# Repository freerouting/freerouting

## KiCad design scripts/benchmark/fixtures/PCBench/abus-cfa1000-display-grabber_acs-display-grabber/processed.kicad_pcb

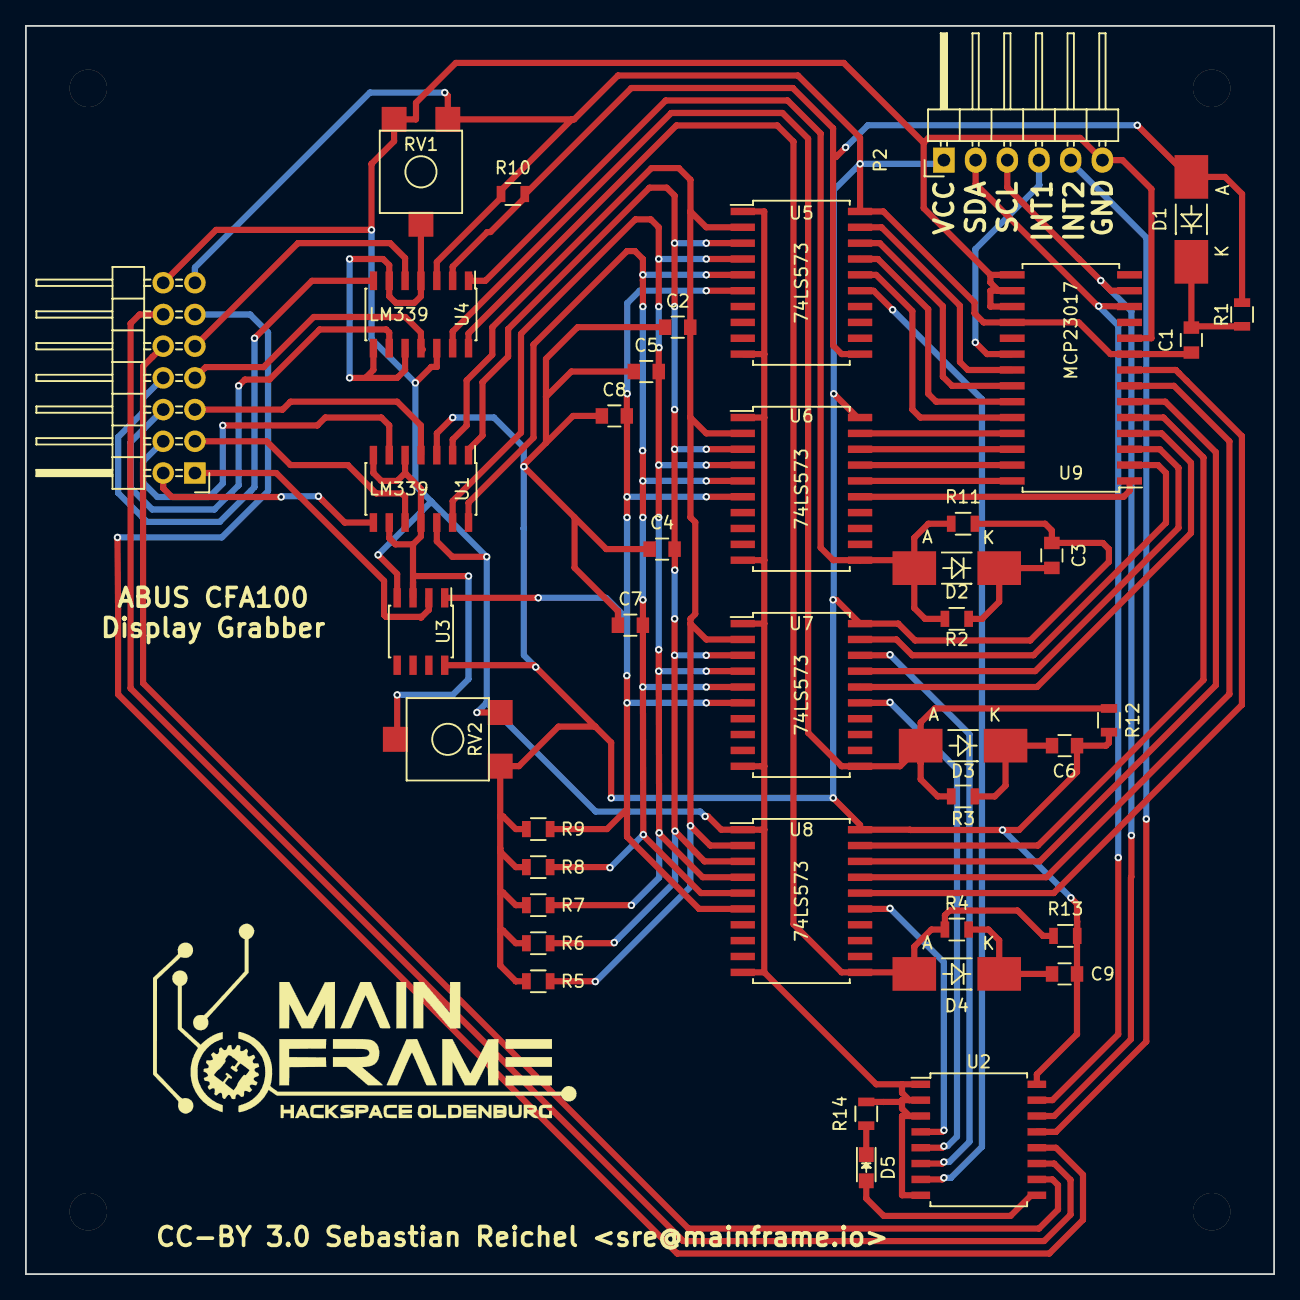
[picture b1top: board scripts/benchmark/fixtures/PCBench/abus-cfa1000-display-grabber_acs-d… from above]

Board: 2 copper layers, 100.0 x 100.0 mm, 41 parts (0 on the bottom side), 55 nets.

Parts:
C1, C3, C6, C9: 20nF; C_0805
C2, C4, C5, C7, C8: 10nF; C_0805
D1, D2, D3, D4: 1N4007; MELF_Handsoldering
D5: Red LED; LED_0805
P1: CONN_02X07; Pin_Header_Angled_2x07
P2: CONN_01X06; Pin_Header_Angled_1x06
R1, R2, R3, R4: 1.8K; R_0805
R5, R6, R7, R8, R9, R10, R11, R12, R13: 3.3K; R_0805
R14: 150; R_0805
RV1, RV2: POT; ACP_CA6
U1, U4: LM339; SOIC-14_3.9x8.7mm_Pitch1.27mm
U2: PCF8574; SOIC-16_7.5x10.3mm_Pitch1.27mm
U3: LM393; SOIC-8_3.9x4.9mm_Pitch1.27mm
U5, U6, U7, U8: 74LS573; SOIC-20_7.5x12.8mm_Pitch1.27mm
U9: MCP23017; SOIC-28_7.5x17.9mm_Pitch1.27mm

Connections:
+5V: C1.2, C2.1, C3.2, C4.1, C5.1, C6.2, C7.1, C8.1, C9.2, P1.13, P2.1, R5.1, R6.1, R7.1, R8.1, R9.1, R10.1, R11.1, R12.1, R13.1, RV1.1, RV2.1, U1.3, U2.16, U3.8, U4.3, U5.20, U6.20, U7.20, U8.20, U9.9, U9.18
/COM0: P1.9, U4.5
/COM0_SEG4: U2.7, U5.15
/COM0clean: D1.2, R1.1, R10.2, U4.2, U5.11
/COM1: P1.8, U4.7
/COM1clean: D2.2, R2.1, R11.2, U4.1, U6.11
/COM2: P1.7, U4.11
/COM2clean: D3.2, R3.1, R12.2, U4.13, U7.11
/COM3: P1.6, U4.9
/COM3_SEG1: U2.6, U7.18
/COM3_SEG4: U2.5, U7.15
/COM3clean: D4.2, R4.1, R13.2, U4.14, U8.11
/COM4_SEG4: U2.4, U8.15
/INT1: P2.4, U9.20
/INT2: P2.5, U2.13
/LED: D5.2, U2.9
/LOCK: P1.10, U2.10
/SCL: P2.3, U2.14, U9.13
/SDA: P2.2, U2.15, U9.12
/SEG0: P1.5, U1.4
/SEG0clean: C2.2, R5.2, U1.2, U5.2, U6.2, U7.2, U8.2
/SEG1: P1.4, U1.6
/SEG1clean: C4.2, R6.2, U1.1, U5.3, U6.3, U7.3, U8.3
/SEG2: P1.3, U1.10
/SEG2clean: C5.2, R7.2, U1.13, U5.4, U6.4, U7.4, U8.4
/SEG3: P1.2, U1.8
/SEG3clean: C7.2, R8.2, U1.14, U5.5, U6.5, U7.5, U8.5
/SEG4: P1.1, U3.2
/SEG4clean: C8.2, R9.2, U3.1, U5.6, U6.6, U7.6, U8.6
/SETUP: P1.11, U2.12
/UNLOCK: P1.12, U2.11
/Vhigh: RV1.2, U4.4, U4.6, U4.8, U4.10
/Vlow: RV2.2, U1.5, U1.7, U1.9, U1.11, U3.3
GND: P1.14, P2.6, R14.2, RV1.3, RV2.3, U1.12, U2.1, U2.2, U2.3, U2.8, U3.4, U4.12, U5.1, U5.10, U6.1, U6.10, U7.1, U7.10, U8.1, U8.10, U9.10, U9.15, U9.16, U9.17
unnamed: C1.1, D1.1, R1.2
unnamed: C3.1, D2.1, R2.2
unnamed: C6.1, D3.1, R3.2
unnamed: C9.1, D4.1, R4.2
unnamed: D5.1, R14.1
unnamed: U5.16, U9.24
unnamed: U5.17, U9.23
unnamed: U5.18, U9.22
unnamed: U5.19, U9.21
unnamed: U6.15, U9.1
unnamed: U6.16, U9.28
unnamed: U6.17, U9.27
unnamed: U6.18, U9.26
unnamed: U6.19, U9.25
unnamed: U7.16, U9.4
unnamed: U7.17, U9.3
unnamed: U7.19, U9.2
unnamed: U8.16, U9.8
unnamed: U8.17, U9.7
unnamed: U8.18, U9.6
unnamed: U8.19, U9.5

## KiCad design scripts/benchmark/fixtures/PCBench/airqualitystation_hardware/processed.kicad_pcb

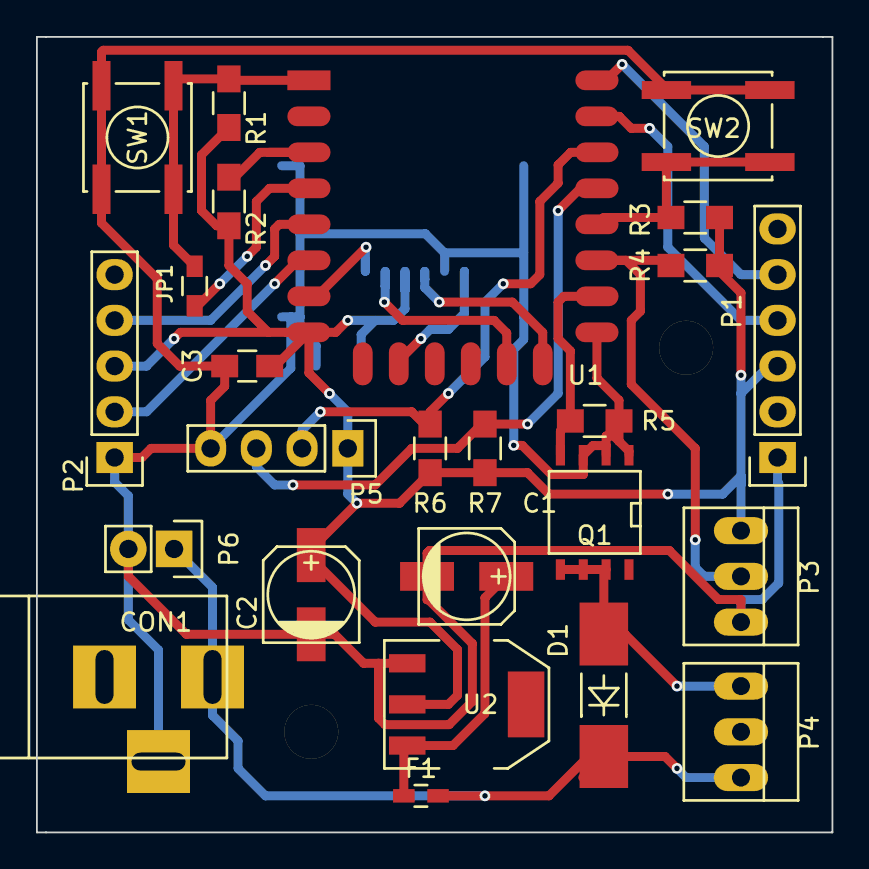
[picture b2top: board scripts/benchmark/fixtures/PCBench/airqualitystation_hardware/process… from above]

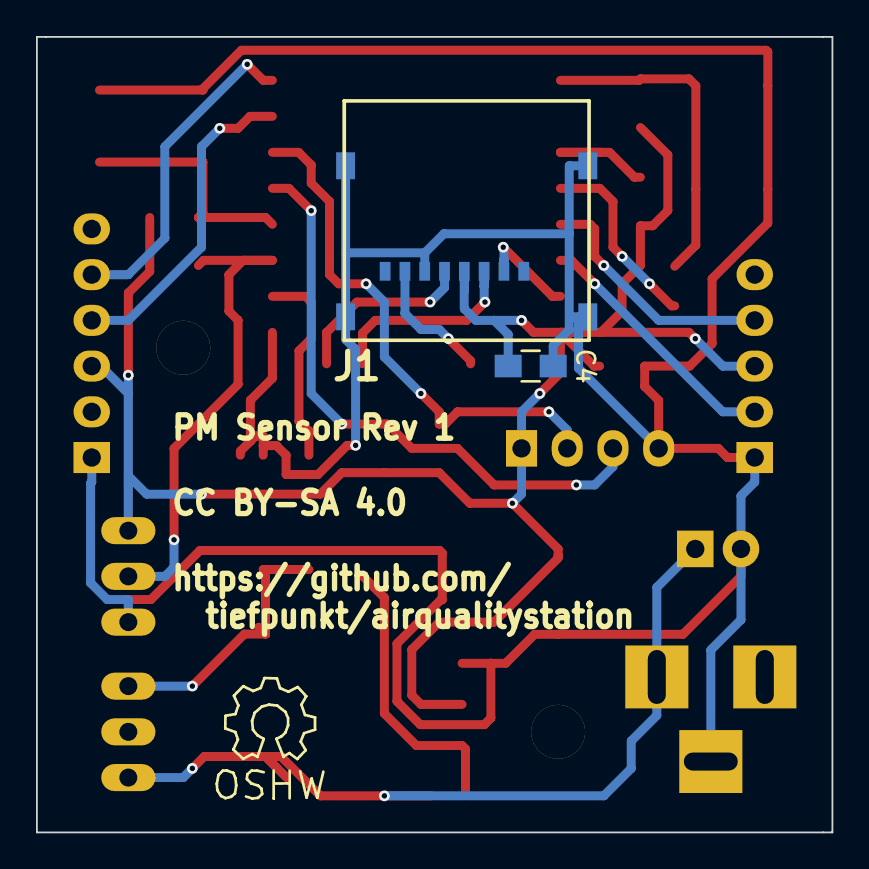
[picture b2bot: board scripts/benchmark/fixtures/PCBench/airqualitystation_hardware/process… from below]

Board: 2 copper layers, 44.2 x 44.2 mm, 27 parts (2 on the bottom side), 21 nets.

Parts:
C1, C2: 10µ; c_elec_5x5.3
C3, C4: 100n; C_0805_HandSoldering
CON1: Power; BARREL_JACK
D1: D; MELF_Handsoldering
F1: 0.1A; C_0603_HandSoldering
J1: MicroSD; MICRO_SD_HINGE_AMP
JP1: Sleep; R_0603_HandSoldering
P1: FTDI ESP; Pin_Header_Straight_1x06
P2: PPD42NS; Pin_Header_Straight_1x05
P3: DHT22; PINHEAD1-3
P4: Fan; PINHEAD1-3
P5: I2C; Pin_Header_Straight_1x04
P6: 5-9V; Pin_Header_Straight_1x02
Q1: IRF7401; SOIC-8-N
R1, R2, R3, R4, R5, R6, R7: 10k; R_0805_HandSoldering
SW1: Reset; SW_SPST_EVPBF
SW2: Flash; SW_SPST_EVPBF
U1: ESP-12E
U2: TS 1117 BCW33; SOT-223

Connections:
+9V: CON1.1, D1.1, F1.1, P4.3, P6.1
GND: C1.2, C2.2, C3.2, C4.2, CON1.3, J1.6, J1.SHLD, P1.1, P2.1, P3.3, P5.4, P6.2, Q1.1, Q1.2, Q1.3, R5.2, SW1.2, SW2.2, U1.15, U2.1
unnamed: C1.1, F1.2, U2.3
unnamed: D1.2, P4.1, Q1.5, Q1.6, Q1.7
unnamed: J1.2, U1.7
unnamed: J1.3, U1.13
unnamed: J1.5, U1.14
unnamed: J1.7, U1.10
unnamed: JP1.1, U1.4
unnamed: JP1.2, R1.2, SW1.1, U1.1
unnamed: P1.4, U1.21
unnamed: P1.5, U1.22
unnamed: P2.2, U1.6
unnamed: P2.4, U1.5
unnamed: P3.2, R4.2, U1.17
unnamed: P5.2, R6.2, U1.20
unnamed: P5.3, R7.2, U1.19
unnamed: Q1.4, R5.1, U1.16
unnamed: R2.2, U1.3
unnamed: R3.2, SW2.1, U1.18
VCC: C2.1, C3.1, C4.1, J1.4, P1.3, P2.3, P3.1, P5.1, R1.1, R2.1, R3.1, R4.1, R6.1, R7.1, U1.8, U2.2

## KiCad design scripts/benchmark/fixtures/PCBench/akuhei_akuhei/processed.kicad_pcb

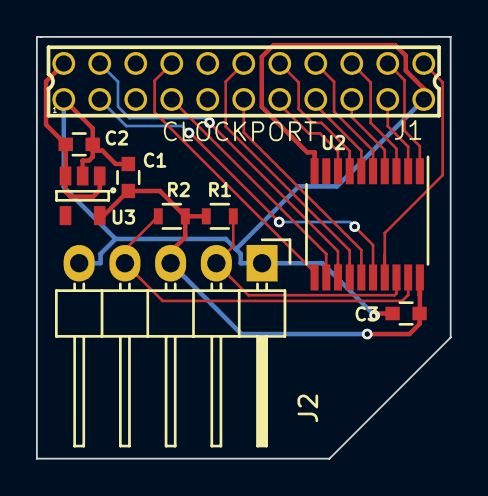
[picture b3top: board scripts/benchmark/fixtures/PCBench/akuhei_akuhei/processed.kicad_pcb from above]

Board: 2 copper layers, 23.0 x 23.4 mm, 9 parts (0 on the bottom side), 20 nets.

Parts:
C1: 1uF; C_0603
C2: 0.1uF; C_0603
C3: 100nF; C_0603
J1: CLOCKPORT; 87758-2216
J2: I2C; Pin_Header_Angled_1x05
R1, R2: 4.7k; R_0603
U2: PCA9564; TSSOP-20_4.4x6.5mm_Pitch0.65mm
U3: TLV70233DBV; SOT-23-5

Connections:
+3V3: C1.1, C3.1, J2.3, R1.2, R2.2, U2.20, U3.5
+5V: C2.1, J1.2, U3.1, U3.3
/A1: J1.12, U2.14
/A2: J1.11, U2.15
/D0: J1.20, U2.1
/D1: J1.19, U2.2
/D2: J1.18, U2.3
/D3: J1.17, U2.4
/D4: J1.16, U2.5
/D5: J1.15, U2.6
/D6: J1.14, U2.7
/D7: J1.13, U2.8
CP_CS: J1.4, U2.13
CP_INT: J1.3, U2.16
CP_IORD: J1.7, U2.12
CP_IOWR: J1.8, U2.11
CP_RESET: J1.22, U2.17
GND: C1.2, C2.2, C3.2, J1.1, J1.21, J2.1, J2.5, U2.10, U3.2
SCL: J2.2, R1.1, U2.18
SDA: J2.4, R2.1, U2.19

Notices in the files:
scripts/benchmark/fixtures/PCBench/abus-cfa1000-display-grabber_acs-display-grabber/processed.kicad_pcb:
CC-BY 3.0 Sebastian Reichel
scripts/benchmark/fixtures/PCBench/airqualitystation_hardware/processed.kicad_pcb:
CC BY-SA 4.0
